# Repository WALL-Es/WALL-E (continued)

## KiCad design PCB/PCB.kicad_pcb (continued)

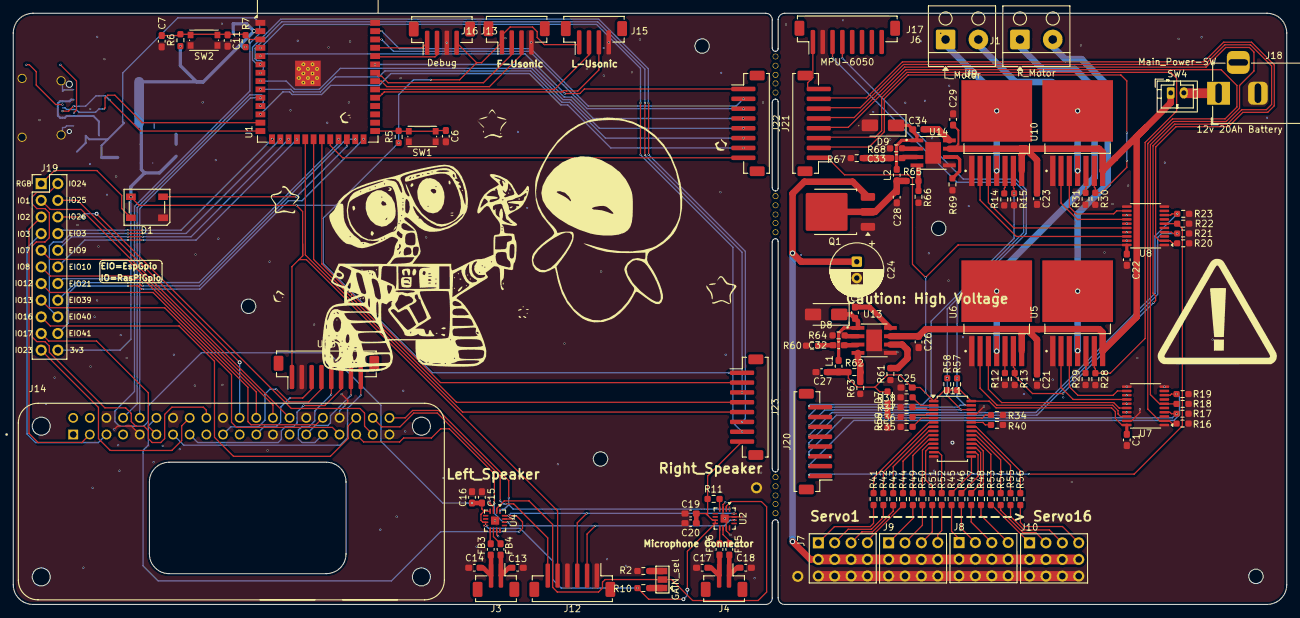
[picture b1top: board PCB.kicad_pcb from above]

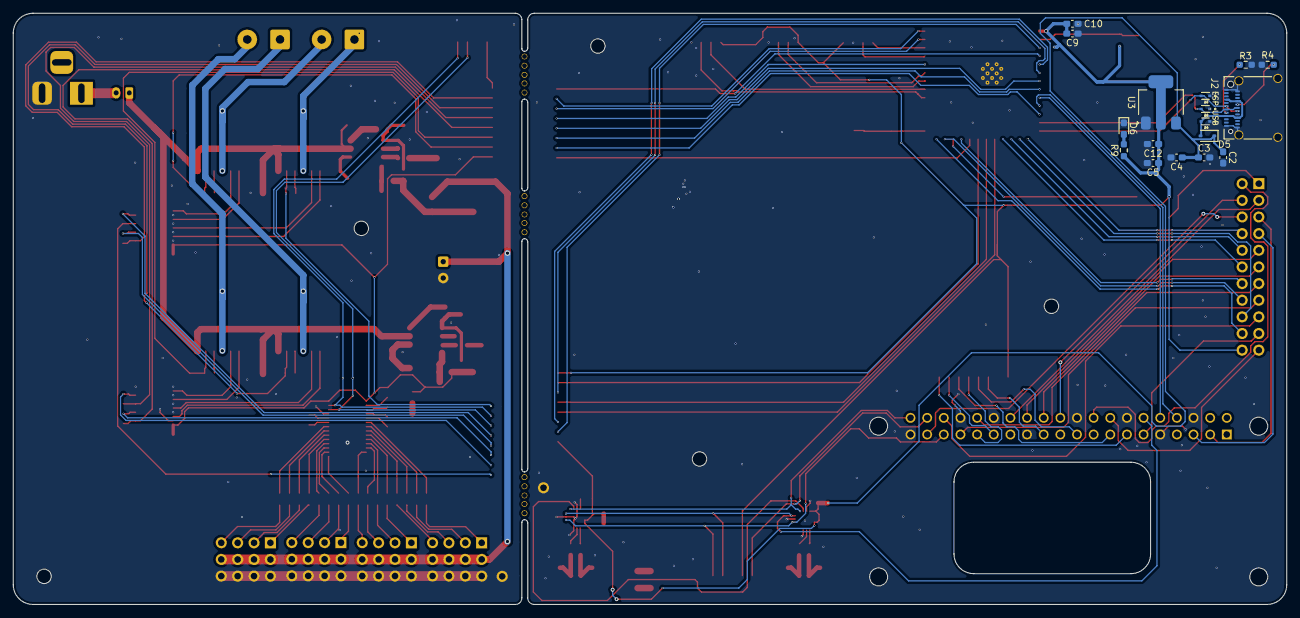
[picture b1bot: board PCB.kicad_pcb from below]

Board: 2 copper layers, 194.3 x 90.2 mm, 147 parts (17 on the bottom side), 168 nets.

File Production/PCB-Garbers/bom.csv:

Designator,Footprint,Quantity,Value,LCSC Part #
"_13, _12, _11, _10, _9, _8, _7, _6, _5, _4, _3, _2, ",,13,,
"C1, C11, C22",0603,3,1uF,
"C10, C12, C15, C20, C4, C6, C7",0603,7,0.1 uF,
"C13, C14, C17, C18, C32, C33",0603,6,220 pF,
"C16, C19, C2, C3, C5, C9",0603,6,10uF,
"C21, C23",0603,2,100 pF,
C24,CP_Radial_D8.0mm_P2.50mm,1,1000 uF,
"C25, C26, C29",0603,3,10 uF,
"C27, C28",0603,2,22 uF,
"C31, C34",0603,2,130 pF,
D1,LED_SK6812_PLCC4_5.0x5.0mm_P3.2mm,1,SK6812,
"D2, D3, D4",TVS_LESD5D5.0CT1G,3,LESD5D5.0CT1G,
D5,D_SOD-323,1,1N5819WS,
"D6, D7",0603,2,LED,
"D8, D9",D_SMA,2,SS34,
"FB3, FB4, FB5, FB6",0603,4,F,
J1,Altech_AK100_1x02_P5.00mm,1,R_Motor,
"J10, J7, J8, J9",Free_GPIO_FP,4,Servos,
J12,JST_ZH_B6B-ZR-SM4-TF_1x06-1MP_P1.50mm_Vertical,1,L-INMP441,
J13,JST_ZH_B4B-ZR-SM4-TF_1x04-1MP_P1.50mm_Vertical,1,Debug,
J14,MODULE_RASPBERRY_PI_ZERO_2_W,1,Raspberry_Pi_Zero,
J15,JST_ZH_B4B-ZR-SM4-TF_1x04-1MP_P1.50mm_Vertical,1,F_HS-SR04+,
J16,JST_ZH_B4B-ZR-SM4-TF_1x04-1MP_P1.50mm_Vertical,1,B_HS-SR04+,
J17,JST_ZH_B8B-ZR-SM4-TF_1x08-1MP_P1.50mm_Vertical,1,MPU-6050,
J18,BarrelJack_Horizontal,1,12v 20Ah Battery,
J19,PinHeader_2x11_P2.54mm_Vertical,1,Free_GPIO,
J2,USB_C_Receptacle_Amphenol_12401610E4-2A_CircularHoles,1,USB_C_Receptacle_USB2.0_16P,
"J20, J21, J22, J23",JST_ZH_B8B-ZR-SM4-TF_1x08-1MP_P1.50mm_Vertical,4,Boards_Connector,
J3,JST_ZH_B2B-ZR-SM4-TF_1x02-1MP_P1.50mm_Vertical,1,Left_Speaker,
J4,JST_ZH_B2B-ZR-SM4-TF_1x02-1MP_P1.50mm_Vertical,1,Right_Speaker,
J5,SolderJumper-3_P1.3mm_Open_Pad1.0x1.5mm,1,GAIN_sel,
J6,Altech_AK100_1x02_P5.00mm,1,L_Motor,
"L1, L2",0603,2,4.7 uH,
Q1,TO-252-3_TabPin2,1,AOD417,
"R10, R2",0603,2,50K,
R11,0603,1,370K,
"R12, R13, R14, R15, R16, R17, R18, R19, R20, R21, R22, R23, R28, R29, R30, R31, R34, R35, R36, R37, R38, R40, R41, R42, R43, R44, R45, R46, R47, R48, R49, R5, R50, R51, R52, R53, R54, R55, R56, R57, R58, R6, R7",0603,43,10k,
"R3, R4",0603,2,5k,
R59,0603,1,470,
"R60, R67",0603,2,68k,
"R61, R69",0603,2,200k,
"R62, R65",0603,2,45k,
"R63, R66",0603,2,8.2k,
"R64, R68",0603,2,1k,
R9,0603,1,7.5k,
"SW1, SW2",SW_Push_1P1T_NO_CK_KMR2,2,SW_MEC_5E,
SW4,JST_PH_B2B-PH-K_1x02_P2.00mm_Vertical,1,Main_Power-SW,
U1,ESP32-S3-WROOM-1,1,ESP32-S3-WROOM-1,
"U10, U5, U6, U9",IC_BTN7960B,4,BTN7960B,
U11,TSSOP-28_4.4x9.7mm_P0.65mm,1,PCA9685PW,
"U13, U14",SOIC12,2,MP1584EN-LF-Z,
U15,JST_ZH_B8B-ZR-SM4-TF_1x08-1MP_P1.50mm_Vertical,1,TFT_128x160,
"U2, U4",TQFN-16-1EP_3x3mm_P0.5mm_EP1.23x1.23mm,2,MAX98357A,
U3,SOT-223-3_TabPin2,1,AMS1117-3.3,
"U7, U8",TSSOP-20_4.4x6.5mm_P0.65mm,2,74HC244,
